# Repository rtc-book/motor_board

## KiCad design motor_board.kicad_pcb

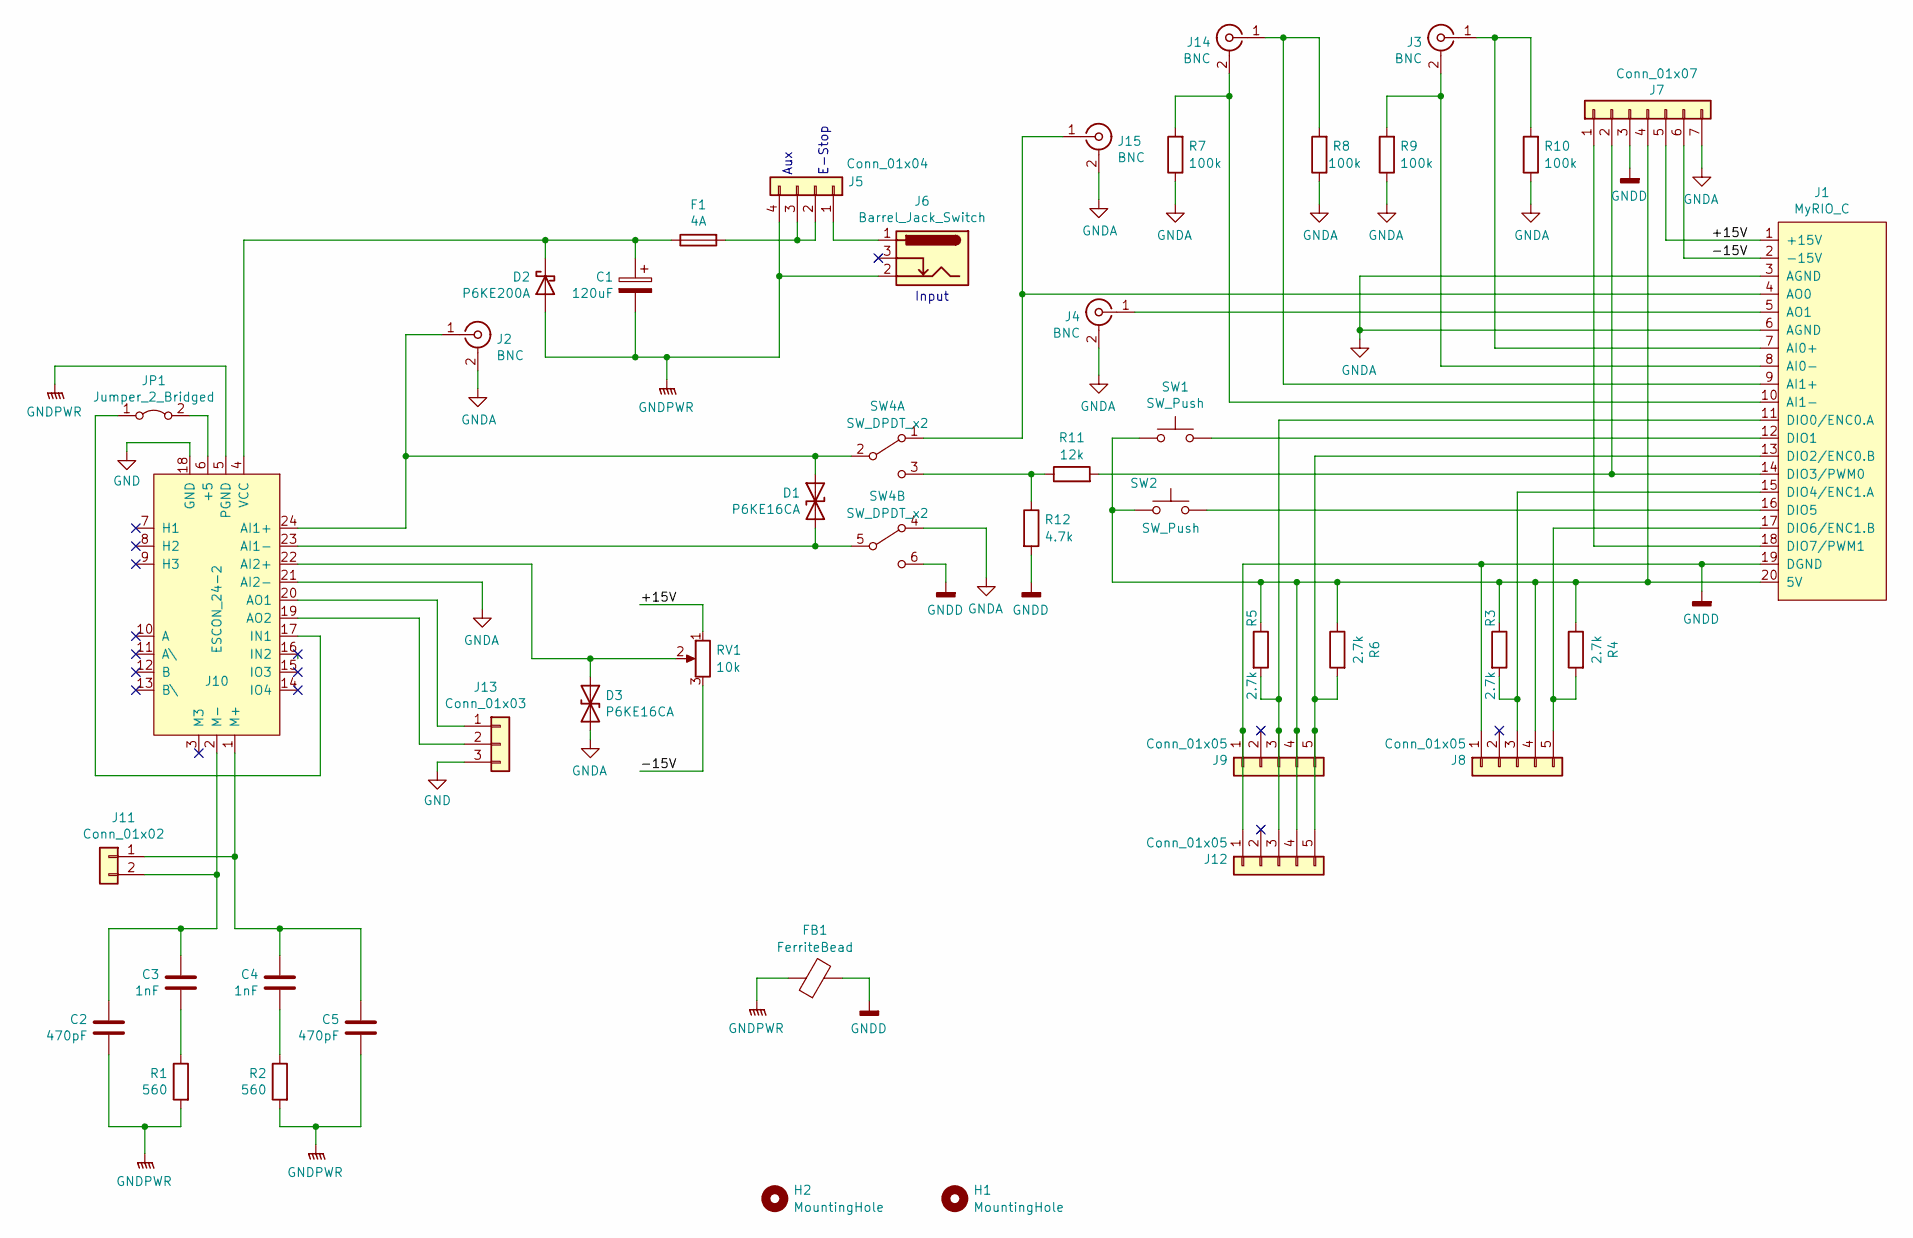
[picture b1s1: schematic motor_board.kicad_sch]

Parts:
C1: 120uF; CP_Radial_D8.0mm_P3.50mm; DigiKey P/N 732-8943-1-ND
C2, C5: 470pF; C_Disc_D4.3mm_W1.9mm_P5.00mm; DigiKey P/N BC2681CT-ND
C3, C4: 1nF; C_Axial_L3.8mm_D2.6mm_P7.50mm_Horizontal; DigiKey P/N 478-10987-1-ND
D1, D3: P6KE16CA; D_DO-15_P10.16mm_Horizontal; DigiKey P/N 13-P6KE16CA/B-ND
D2: P6KE200A; D_DO-15_P10.16mm_Horizontal; DigiKey P/N P6KE200ALFCT-ND
F1: 4A; Fuseholder_Cylinder-5x20mm_Schurter_0031_8201_Horizontal_Op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; DigiKey P/N 0617004.MXP-ND, 732-11376-ND
FB1: FerriteBead; L_Axial_L7.0mm_D3.3mm_P10.16mm_Horizontal_Fastron_MICC; DigiKey P/N 1934-1414-1-ND
H1, H2: MountingHole; MountingHole_#6
J1: MyRIO_C; C_Connector; DigiKey P/N ED3077-ND
J2, J3, J4, J14, J15: BNC; Vertical_BNC_Amphenol_112536; DigiKey P/N ACX1053-ND
J5: Conn_01x04; TerminalBlock_Phoenix_PT-1,5-4-5.0-H_1x04_P5.00mm_Horizontal; DigiKey P/N 102-6136-ND
J6: Barrel_Jack_Switch; BarrelJack_Horizontal; DigiKey P/N 839-54-00167-ND
J7: Conn_01x07; PinSocket_1x07_P2.54mm_Vertical; DigiKey P/N S7005-ND
J8, J9: Conn_01x05; PinHeader_1x05_P2.54mm_Vertical; DigiKey P/N 2057-PH1-05-UA-ND
J10: ESCON_24-2; DigiKey P/N S7009-ND, S7011-ND
J11: Conn_01x02; TerminalBlock_Phoenix_PT-1,5-2-5.0-H_1x02_P5.00mm_Horizontal; DigiKey P/N 102-6134-ND
J12: Conn_01x05; Encoder_and_Motor_Mount; DigiKey P/N S6103-ND
J13: Conn_01x03; PinSocket_1x03_P2.54mm_Vertical; DigiKey P/N S7036-ND
JP1: Jumper_2_Bridged; PinHeader_1x02_P2.54mm_Vertical; DigiKey P/N 2057-PH1-02-UA-ND, S9000-ND
R1, R2: 560; R_Axial_DIN0207_L6.3mm_D2.5mm_P7.62mm_Horizontal; DigiKey P/N 560WCT-ND
R3, R4, R5, R6: 2.7k; R_Axial_DIN0204_L3.6mm_D1.6mm_P5.08mm_Horizontal; DigiKey P/N CF18JT2K70CT-ND
R7, R8, R9, R10: 100k; R_Axial_DIN0204_L3.6mm_D1.6mm_P5.08mm_Horizontal; DigiKey P/N CF18JT100KCT-ND
R11: 12k; R_Axial_DIN0204_L3.6mm_D1.6mm_P5.08mm_Horizontal; DigiKey P/N 13-MFR-12FTF52-12KCT-ND
R12: 4.7k; R_Axial_DIN0204_L3.6mm_D1.6mm_P5.08mm_Horizontal; DigiKey P/N 13-MFR-12FTF52-4K7CT-ND
RV1: 10k; Potentiometer_Piher_PT-10-V10_Vertical; DigiKey P/N 1993-1116-ND
SW1, SW2: SW_Push; SW_PUSH_6mm_H5mm; DigiKey P/N CKN9093-ND
SW4: SW_DPDT_x2; TE Connectivity MHS DPDT Slide Switch; DigiKey P/N 450-1574-ND

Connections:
/+15V: J1.1 (+15V), J7.5, RV1.1
/-15V: J1.2 (-15V), J7.6, RV1.3
GND: J10.18 (GND), J13.3
GNDA: D3.2 (A2), J1.3 (AGND), J1.6 (AGND), J2.2 (Ext), J4.2 (Ext), J7.7, J10.21 (AI2-), J15.2 (Ext), R7.1, R8.1, R9.1, R10.1, SW4.4 (A)
GNDD: FB1.2, J1.19 (DGND), J7.3, J8.1, J9.1, J12.1, R12.2, SW4.6 (C)
GNDPWR: C1.2, C2.2, C5.2, D2.2 (A), FB1.1, J5.4, J6.2, J10.5 (PGND), R1.2, R2.2
unnamed: C3.2, R1.1
unnamed: C4.2, R2.1
unnamed: D1.1 (A1), J2.1 (In), J10.24 (AI1+), SW4.2 (B)
unnamed: D1.2 (A2), J10.23 (AI1-), SW4.5 (B)
unnamed: C1.1, D2.1 (K), F1.1, J10.4 (VCC)
unnamed: D3.1 (A1), J10.22 (AI2+), RV1.2
unnamed: J1.20 (5V), J7.4, J8.4, J9.4, J12.4, R3.1, R4.1, R5.1, R6.1, SW1.2, SW2.2
unnamed: J1.7 (AI0+), J3.1 (In), R10.2
unnamed: J1.8 (AI0-), J3.2 (Ext), R9.2
unnamed: J1.9 (AI1+), J14.1 (In), R8.2
unnamed: J1.10 (AI1-), J14.2 (Ext), R7.2
unnamed: J1.4 (AO0), J15.1 (In), SW4.1 (A)
unnamed: J1.5 (AO1), J4.1 (In)
unnamed: J1.11 (DIO0/ENC0.A), J9.3, J12.3, R5.2
unnamed: J1.12 (DIO1), SW1.1
unnamed: J1.13 (DIO2/ENC0.B), J9.5, J12.5, R6.2
unnamed: J1.14 (DIO3/PWM0), J7.2, R11.2
unnamed: J1.15 (DIO4/ENC1.A), J8.3, R3.2
unnamed: J1.16 (DIO5), SW2.1
unnamed: J1.17 (DIO6/ENC1.B), J8.5, R4.2
unnamed: J1.18 (DIO7/PWM1), J7.1
unnamed: J5.1, J6.1
unnamed: F1.2, J5.2, J5.3
unnamed: J10.6 (+5), JP1.2 (B)
unnamed: J10.20 (AO1), J13.1
unnamed: J10.19 (AO2), J13.2
unnamed: J10.17 (IN1), JP1.1 (A)
unnamed: C4.1, C5.1, J10.1 (M+), J11.1
unnamed: C2.1, C3.1, J10.2 (M-), J11.2
unnamed: R11.1, R12.1, SW4.3 (C)

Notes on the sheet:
Aux
Input
E-Stop

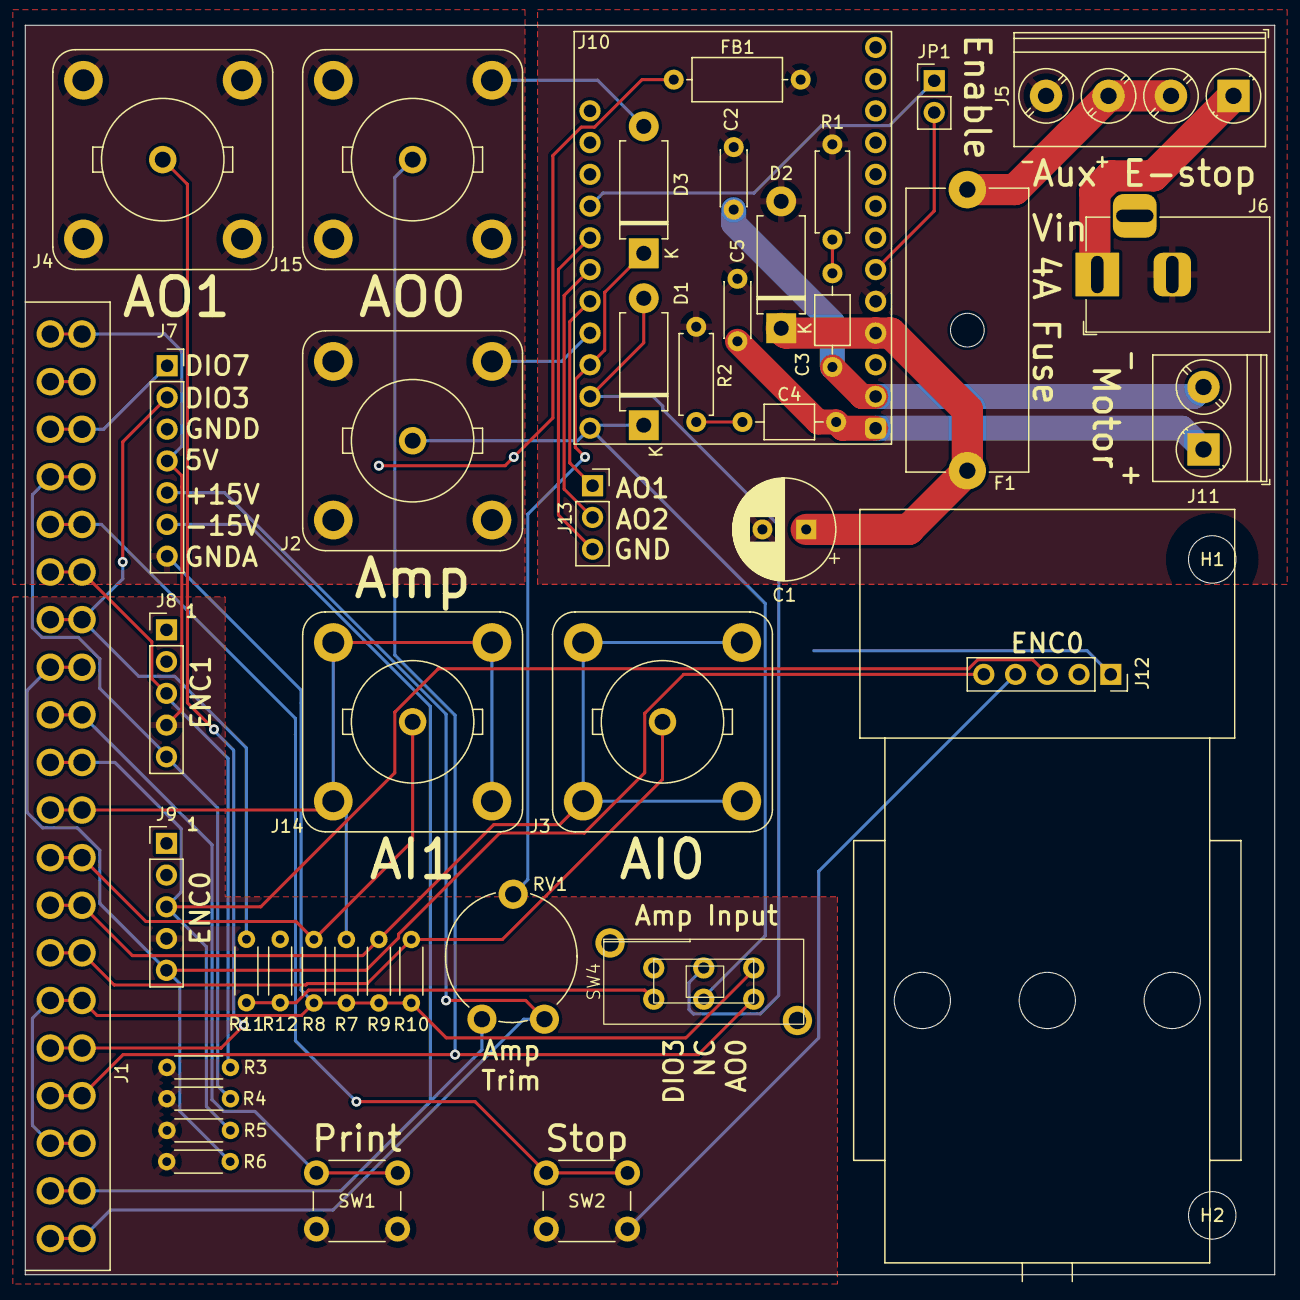
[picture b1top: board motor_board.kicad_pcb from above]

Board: 2 copper layers, 100.0 x 100.0 mm, 44 parts (0 on the bottom side), 36 nets.

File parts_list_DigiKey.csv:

1,732-8943-1-ND,120uF
2,BC2681CT-ND,470pF
2,478-10987-1-ND,1nF
1,P6KE200ALFCT-ND,P6KE200A
1,0617004.MXP-ND,4A
1,732-11376-ND,4A
1,ED3077-ND,MyRIO_C
1,S7009-ND,ESCON_24-2
1,S7011-ND,ESCON_24-2
2,2057-RF1-01K-D-00-50-BK-HDW-ND,BNC
1,S7006-ND,Conn_01x08
2,2057-PH1-05-UA-ND,Conn_01x05
1,102-6136-ND,Conn_01x04
1,102-6134-ND,Conn_01x02
1,S6103-ND,Conn_01x05
1,839-54-00167-ND,Barrel_Jack_Switch
2,560WCT-ND,560
4,CF18JT2K70CT-ND,2.7k
2,CKN9093-ND,SW_Push

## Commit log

2022-11-16 removed the voltage regulator and shrunk the board
2022-11-16 removed the regulator design script since I removed the regulator
2022-11-16 added files for manufacturing
2022-12-23 changed the switch labels and moved some things around
2022-12-24 added TVS diodes for safety
2023-04-30 twisted the motor and added a couple connectors
2023-04-30 renumbered components
2023-04-30 changed date
2023-05-02 change test points to pin sockets
2023-07-05 the first version produced
2023-09-17 board v1.1
2023-09-17 removing files because I upgraded KiCAD
2023-09-30 fixed the motor label polarity issue
2023-12-12 added a couple mounting holes and updated the motor mount
2024-02-13 changed to a bidirectional TVS diode for protection on the amp analog inputs
2024-08-09 updated the board with a 90 degree twisted motor and 5 bncs plus amp input switch and trim.
2024-08-12 got the motor rotated back 90 degrees to its original orientation
2024-08-12 adding v2 gerbers
2024-08-13 removing digikey partslist because it is out of date
2024-08-23 added a resistor divider to the PWM amp input
2024-10-16 updated the board to use a 10k pot that is hopefully more heat resistant and has longer leads.
2024-11-04 Adding the design notebook of the updated resistor divider
2024-11-11 added a resistor divider to get the correct current for lab 4, added DIO3 to the aux header, and changed to a more durable 10 k put to keep from overloading the +/-15 V supply.
2024-11-24 The final design
